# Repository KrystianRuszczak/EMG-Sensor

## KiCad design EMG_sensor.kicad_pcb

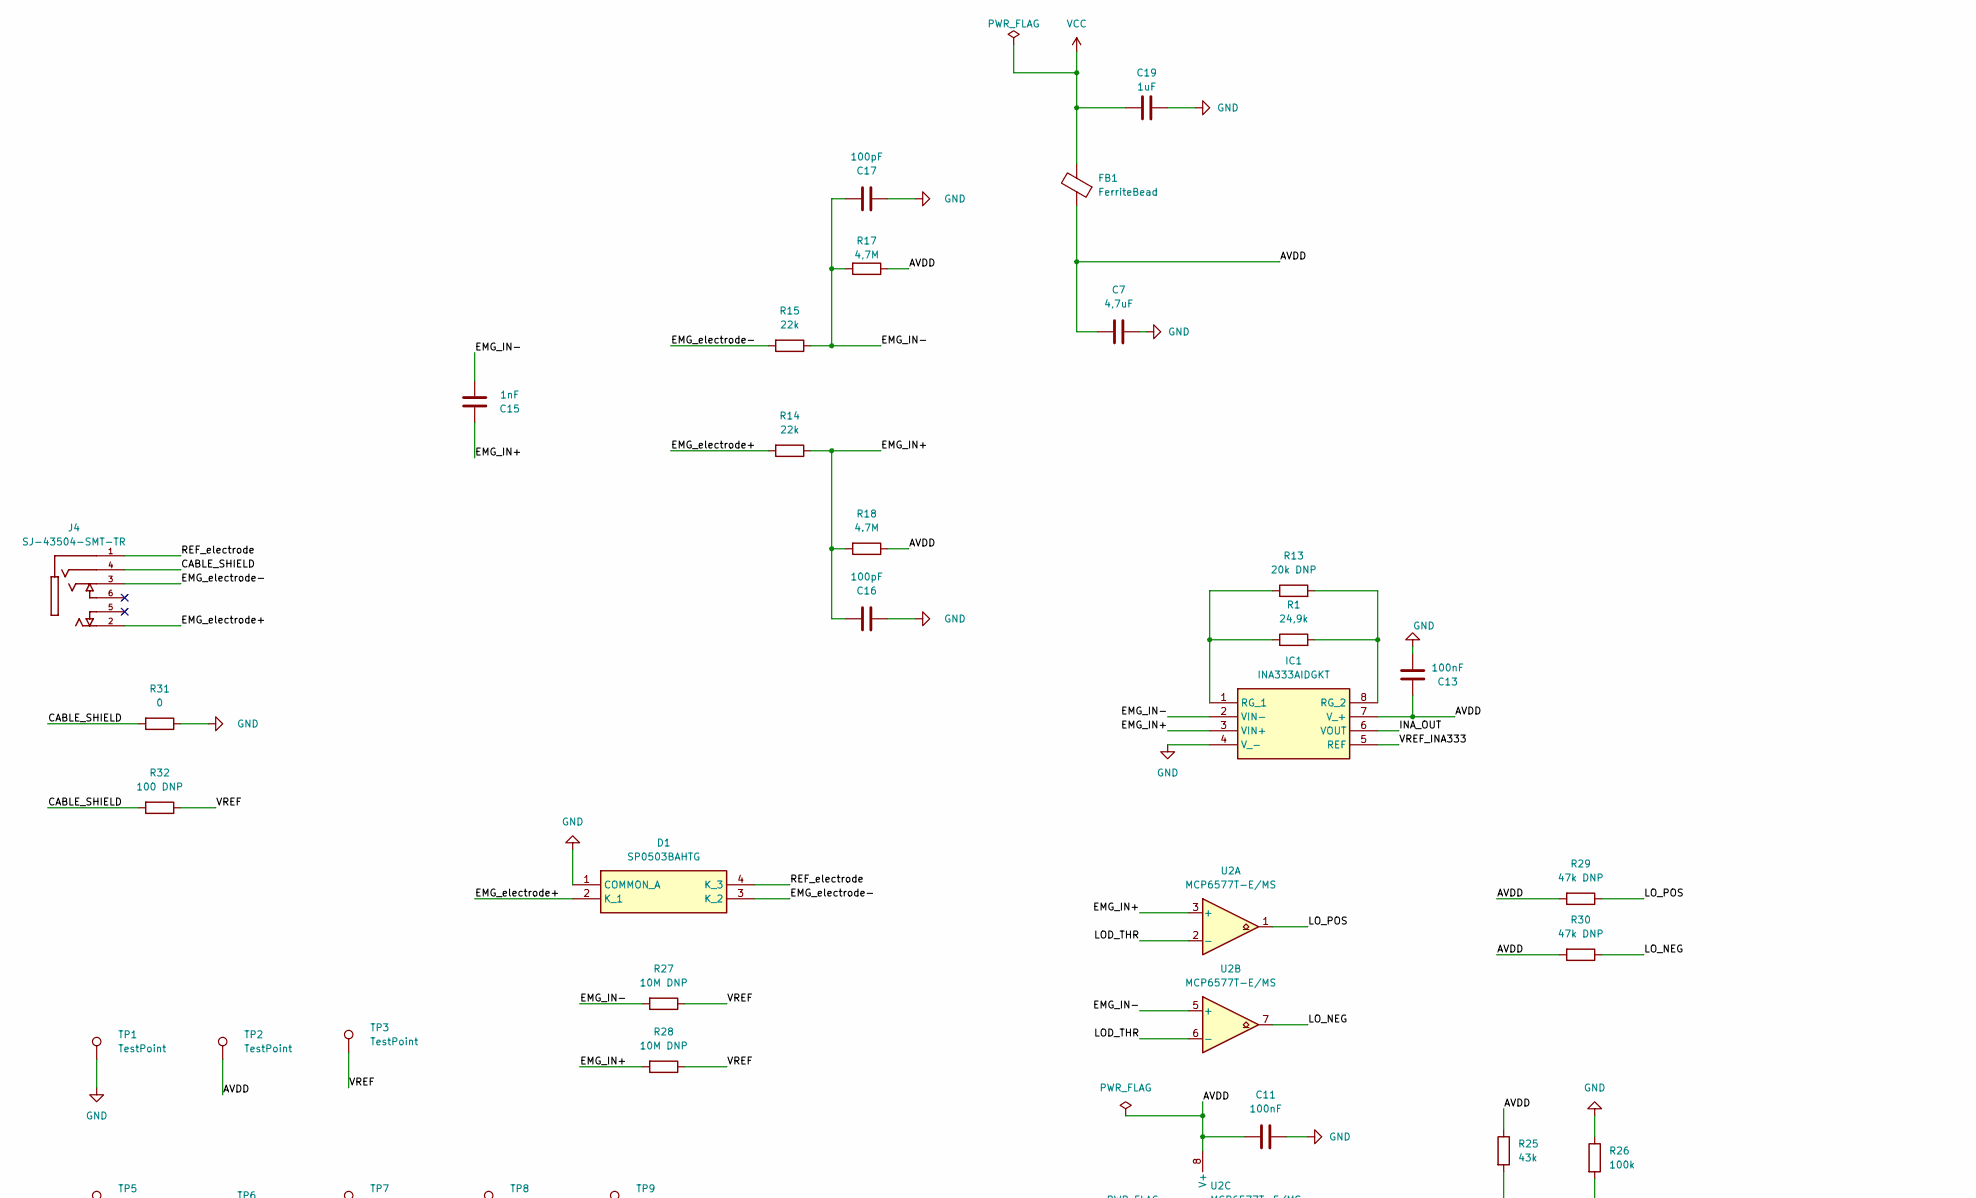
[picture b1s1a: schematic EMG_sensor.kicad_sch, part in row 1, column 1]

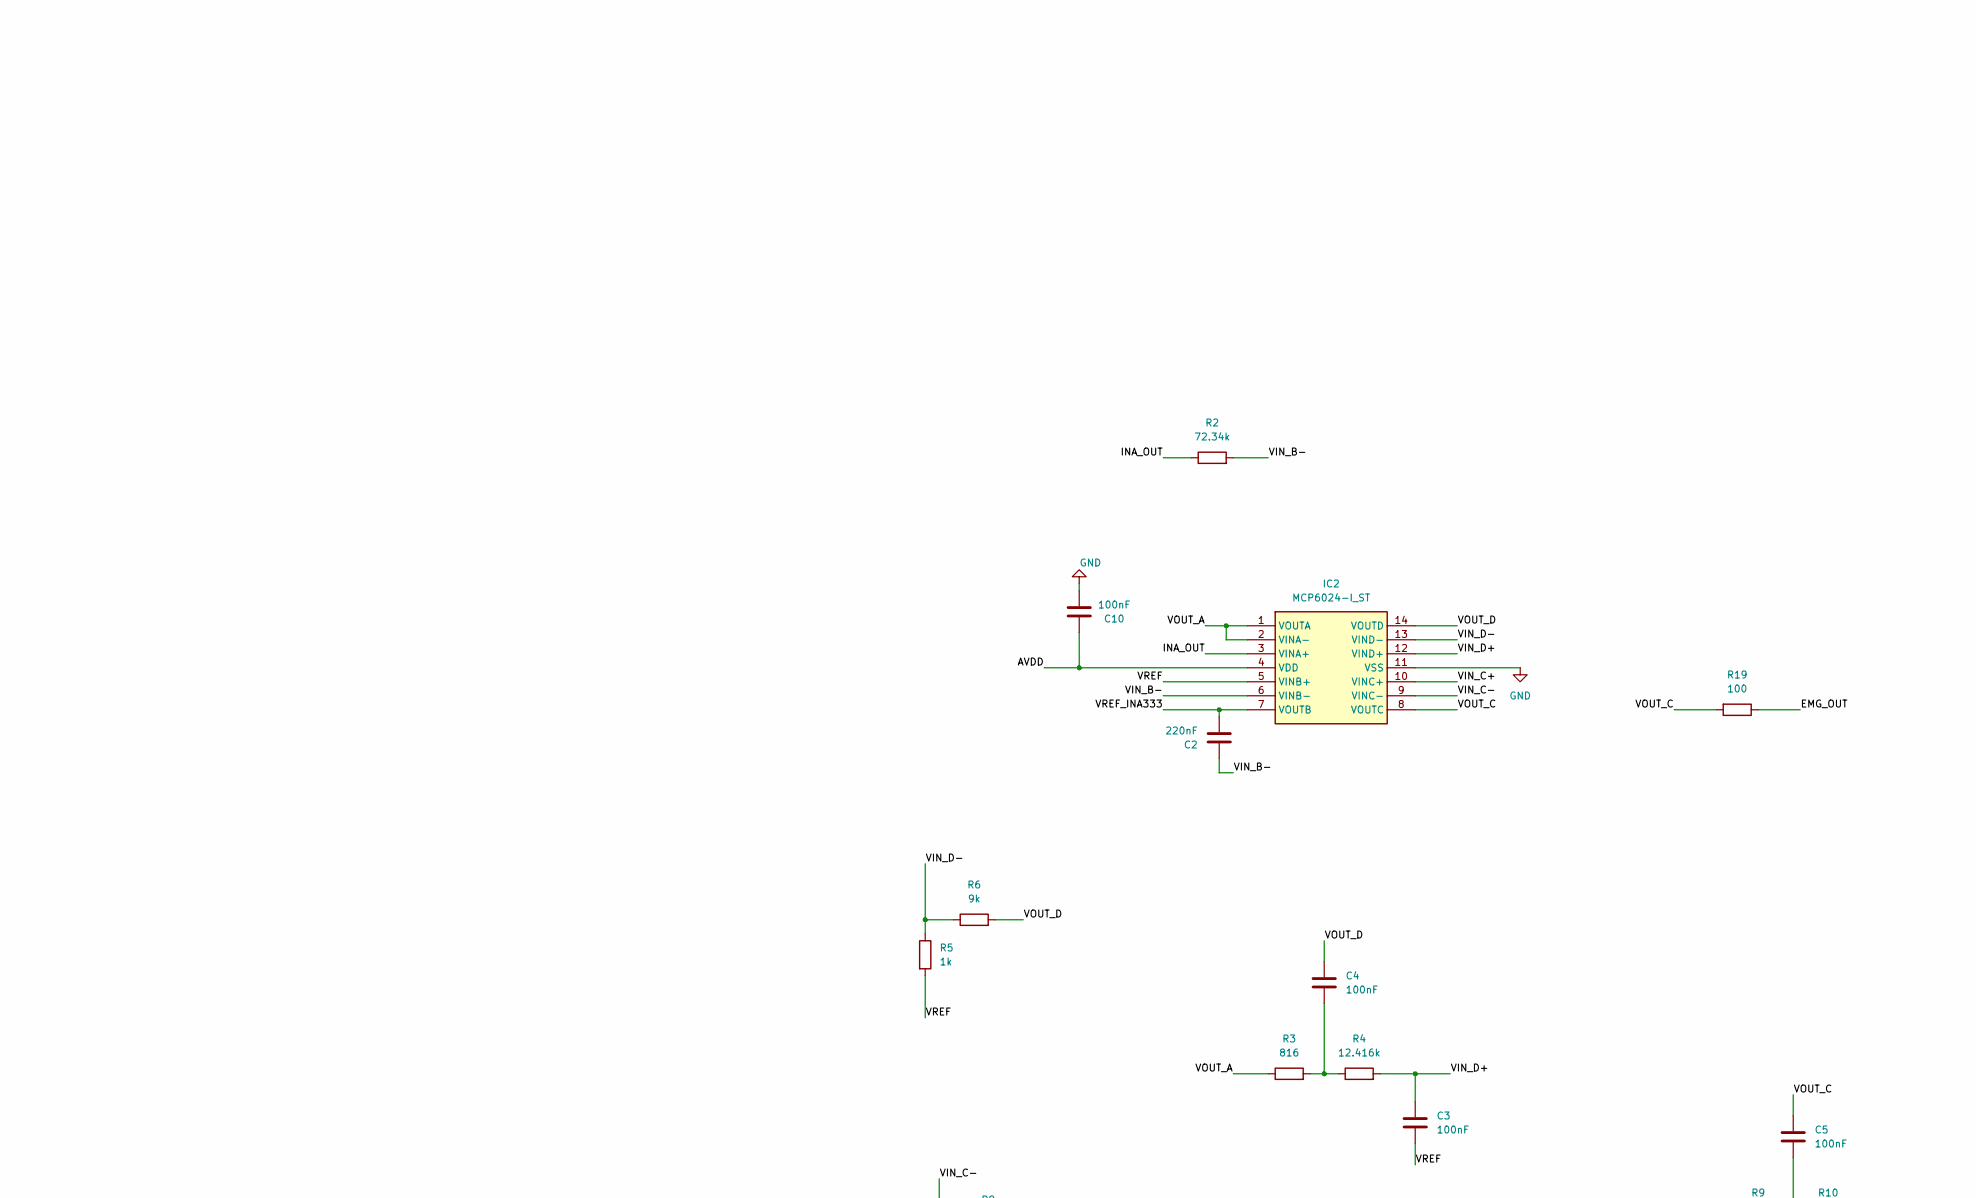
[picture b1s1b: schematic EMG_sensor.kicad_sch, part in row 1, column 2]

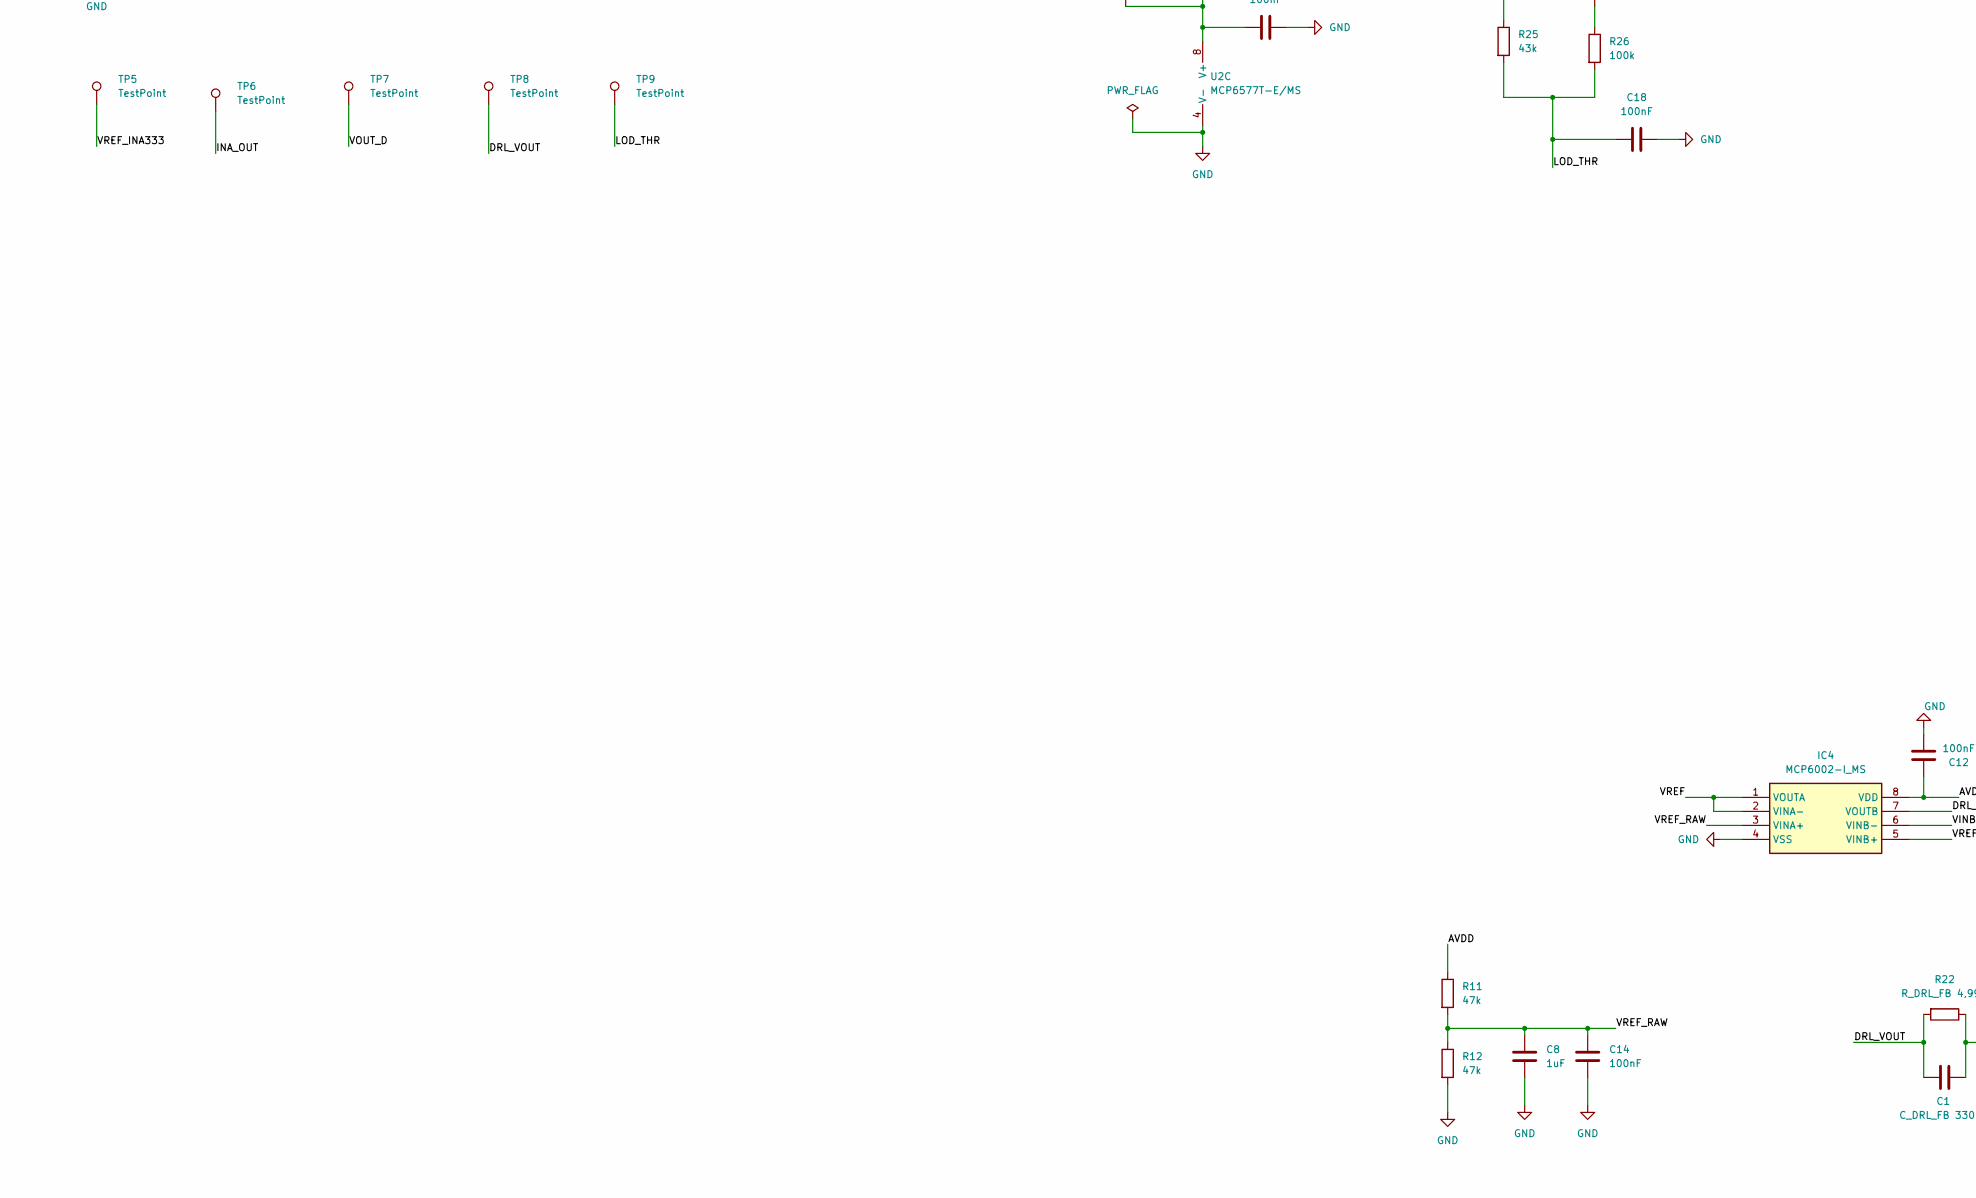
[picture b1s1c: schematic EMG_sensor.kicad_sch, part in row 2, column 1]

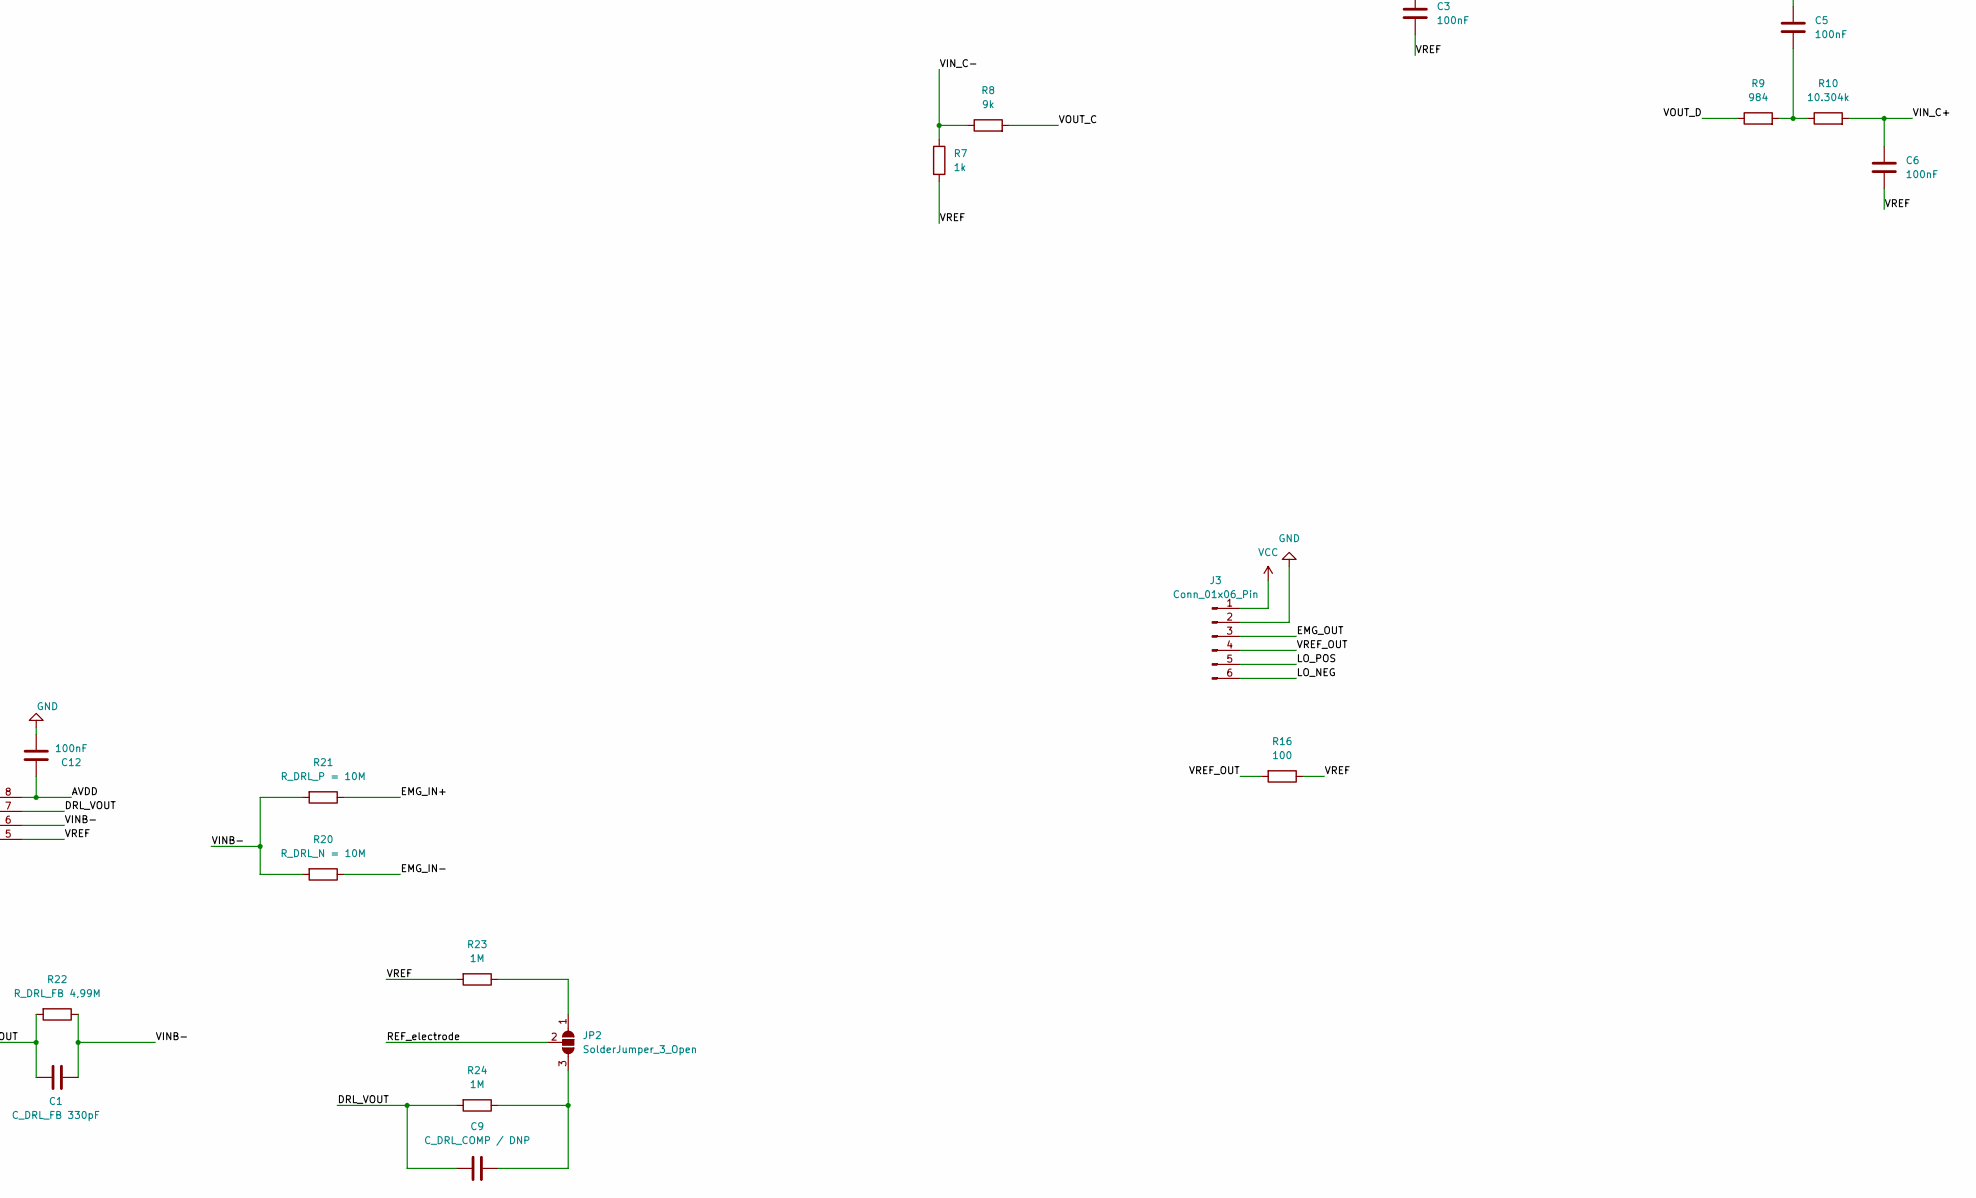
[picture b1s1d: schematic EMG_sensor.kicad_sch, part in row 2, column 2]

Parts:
C1: C_DRL_FB 330pF; C_0402_1005Metric
C2: 220nF; C_0805_2012Metric
C3, C4, C5, C6: 100nF; C_1206_3216Metric
C7: 4,7uF; C_0805_2012Metric
C8, C19: 1uF; C_0603_1608Metric
C9: C_DRL_COMP / DNP; C_0603_1608Metric
C10, C11, C12, C13, C14, C18: 100nF; C_0402_1005Metric
C15: 1nF; C_0402_1005Metric
C16, C17: 100pF; C_0402_1005Metric
D1: SP0503BAHTG; Manufacturer_Part_Number SP0503BAHTG
FB1: FerriteBead; L_0603_1608Metric
IC1: INA333AIDGKT; SOP65P490X110-8N; Manufacturer_Part_Number INA333AIDGKT
IC2: MCP6024-I_ST; SOP65P640X120-14N; Manufacturer_Part_Number MCP6024-I/ST
IC4: MCP6002-I_MS; SOP65P490X110-8N; Manufacturer_Part_Number MCP6002-I/MS
J3: Conn_01x06_Pin; JST_SH_SM06B-SRSS-TB_1x06-1MP_P1.00mm_Horizontal
J4: SJ-43504-SMT-TR; CUI_SJ-43504-SMT-TR; PARTREV 10/08/2019
JP2: SolderJumper_3_Open; SolderJumper-3_P1.3mm_Open_RoundedPad1.0x1.5mm_NumberLabels
R1: 24,9k; R_0603_1608Metric
R2: 72.34k; R_0603_1608Metric
R3: 816; R_0603_1608Metric
R4: 12.416k; R_0603_1608Metric
R5, R7: 1k; R_0603_1608Metric
R6, R8: 9k; R_0603_1608Metric
R9: 984; R_0603_1608Metric
R10: 10.304k; R_0603_1608Metric
R11, R12: 47k; R_0603_1608Metric
R13: 20k DNP; R_0402_1005Metric
R14, R15: 22k; R_0603_1608Metric
R16, R19: 100; R_0402_1005Metric
R17: 4,7M; R_0603_1608Metric
R18: 4.7M; R_0603_1608Metric
R20: R_DRL_N = 10M; R_0603_1608Metric
R21: R_DRL_P = 10M; R_0603_1608Metric
R22: R_DRL_FB 4,99M; R_0603_1608Metric
R23, R24: 1M; R_0603_1608Metric
R25: 43k; R_0402_1005Metric
R26: 100k; R_0402_1005Metric
R27, R28: 10M DNP; R_0603_1608Metric
R29, R30: 47k DNP; R_0402_1005Metric
R31: 0; R_0402_1005Metric
R32: 100 DNP; R_0402_1005Metric
TP1, TP2, TP3, TP5, TP6, TP7, TP8, TP9: TestPoint; TestPoint_Pad_D1.0mm
U2: MCP6577T-E/MS; MSOP-8_3x3mm_P0.65mm

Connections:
/AVDD: C7.1, C10.1, C11.2, C12.1, C13.1, FB1.1, IC1.7 (V_+), IC2.4 (VDD), IC4.8 (VDD), R11.1, R17.1, R18.1, R25.1, R29.2, R30.2, TP2.1 (1_1), U2.8 (V+)
/CABLE_SHIELD: J4.4, R31.2, R32.2
/DRL_VOUT: C1.2, C9.2, IC4.7 (VOUTB), R22.2, R24.2, TP8.1 (1_1)
/EMG_IN+: C15.1, C16.2, IC1.3 (VIN+), R14.1, R18.2, R21.1, R28.2, U2.3 (+)
/EMG_IN-: C15.2, C17.2, IC1.2 (VIN-), R15.1, R17.2, R20.1, R27.2, U2.5 (+)
/EMG_OUT: J3.3, R19.1
/EMG_electrode+: D1.2 (K_1), J4.2, R14.2
/EMG_electrode-: D1.3 (K_2), J4.3, R15.2
/INA_OUT: IC1.6 (VOUT), IC2.3 (VINA+), R2.1, TP6.1 (1_1)
/LOD_THR: C18.2, R25.2, R26.2, TP9.1 (1_1), U2.2 (-), U2.6 (-)
/LO_NEG: J3.6, R30.1, U2.7
/LO_POS: J3.5, R29.1, U2.1
/REF_electrode: D1.4 (K_3), J4.1, JP2.2 (C)
/VINB-: C1.1, IC4.6 (VINB-), R20.2, R21.2, R22.1
/VIN_B-: C2.2, IC2.6 (VINB-), R2.2
/VIN_C+: C6.2, IC2.10 (VINC+), R10.2
/VIN_C-: IC2.9 (VINC-), R7.1, R8.1
/VIN_D+: C3.2, IC2.12 (VIND+), R4.2
/VIN_D-: IC2.13 (VIND-), R5.1, R6.1
/VOUT_A: IC2.1 (VOUTA), IC2.2 (VINA-), R3.1
/VOUT_C: C5.1, IC2.8 (VOUTC), R8.2, R19.2
/VOUT_D: C4.1, IC2.14 (VOUTD), R6.2, R9.1, TP7.1 (1_1)
/VREF: C3.1, C6.1, IC2.5 (VINB+), IC4.1 (VOUTA), IC4.2 (VINA-), IC4.5 (VINB+), R5.2, R7.2, R16.1, R23.2, R27.1, R28.1, R32.1, TP3.1 (1_1)
/VREF_INA333: C2.1, IC1.5 (REF), IC2.7 (VOUTB), TP5.1 (1_1)
/VREF_OUT: J3.4, R16.2
/VREF_RAW: C8.1, C14.1, IC4.3 (VINA+), R11.2, R12.1
GND: C7.2, C8.2, C10.2, C11.1, C12.2, C13.2, C14.2, C16.1, C17.1, C18.1, C19.1, D1.1 (COMMON_A), IC1.4 (V_-), IC2.11 (VSS), IC4.4 (VSS), J3.2, R12.2, R26.1, R31.1, TP1.1 (1_1), U2.4 (V-)
unnamed: C4.2, R3.2, R4.1
unnamed: C5.2, R9.2, R10.1
unnamed: IC1.1 (RG_1), R1.1, R13.1
unnamed: IC1.8 (RG_2), R1.2, R13.2
unnamed: JP2.1 (A), R23.1
unnamed: C9.1, JP2.3 (B), R24.1
VCC: C19.2, FB1.2, J3.1

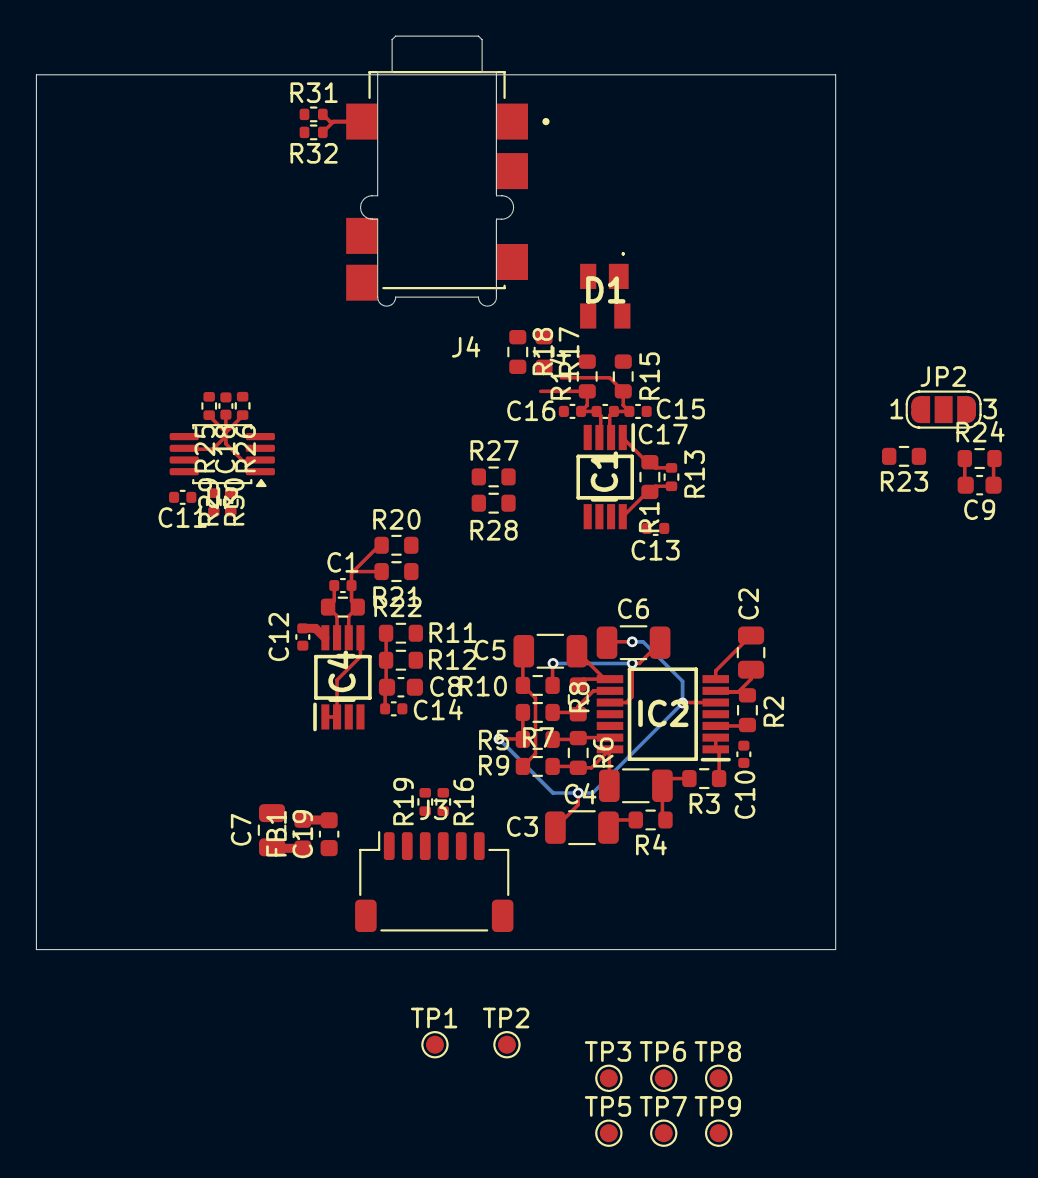
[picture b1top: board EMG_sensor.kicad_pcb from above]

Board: 4 copper layers, 44.4 x 50.8 mm, 68 parts (0 on the bottom side), 34 nets.
